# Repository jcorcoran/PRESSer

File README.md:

# PRESSer
FRC pressure switch breakout board

* Soldered directly to the back of the Nason Pressure switch. Tabs get covered in heat shrink.
* Allows for easy testing of `shorting` the pressure switch during inspection by holing down the onboard button (to check dump valve on over-pressurization)
* Adds a 2.54" pin header for easy wiring into the switch.

This is a [KiCad](https://www.kicad.org/download/) 6.x project.  
The gerbers can be used to order from any PCB fab house.

Panelized PCBs were generated using the [kikit](https://github.com/yaqwsx/KiKit/) project using the following command:

```
kikit panelize --layout "grid; rows: 3; cols: 3; space: 2mm" --tabs "annotation" --source "tolerance: 5mm" --cuts "mousebites; drill: 0.5mm; spacing: 1mm; prolong: 0.5mm" --post "millradius: 1mm" PressureSwitchBreakout.kicad_pcb panel.kicad_pcb
```

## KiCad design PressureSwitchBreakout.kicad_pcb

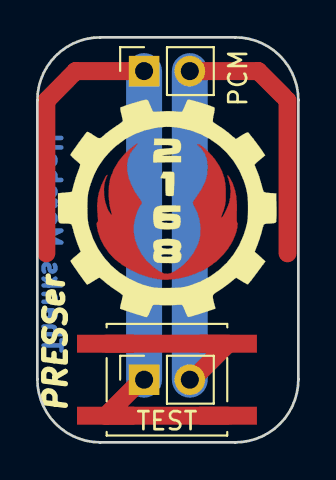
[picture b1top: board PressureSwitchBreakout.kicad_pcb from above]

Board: 2 copper layers, 14.5 x 22.5 mm, 3 parts (0 on the bottom side), 2 nets.

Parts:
J1: TEST; PinSocket_1x02_P2.54mm_Vertical
PCM: PCM; PinSocket_1x02_P2.54mm_Vertical
TEST: TEST; SW_SPST_EVQQ2

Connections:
unnamed: J1.1, PCM.1, TEST.2
unnamed: J1.2, PCM.2, TEST.1

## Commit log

2021-12-29 Update to kicad 6.0 export gerbers panelize using kikit
2021-12-29 add image of PCB
2021-12-29 save
